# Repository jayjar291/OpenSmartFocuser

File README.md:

# OpenSmartFocuser

OpenSmartFocuser is an open-source telescope focuser project with:
- ESP32-S3 firmware (display/menu, motor control, serial command handling)
- an INDI driver scaffold for host-side integration
- hardware design files for PCB and related fabrication assets

## Build Targets

- `firmware/` contains the PlatformIO project for the device firmware.
- `drivers/indi/` contains the CMake-based INDI focuser driver.

## Folder Structure

```text
OpenSmartFocuser/
├── .github/
│   ├── ISSUE_TEMPLATE/        # GitHub issue templates
│   └── workflows/             # CI workflows (firmware and INDI driver builds)
├── docs/                      # Project documentation and operating notes
├── drivers/
│   └── indi/                  # INDI driver scaffold and CMake config
├── firmware/
│   ├── include/               # Firmware headers/config
│   ├── src/                   # Firmware source code
│   ├── platformio.ini         # PlatformIO project config
│   └── backup/                # Local backup files
└── hardware/
    ├── README.md              # Hardware folder overview
    ├── cad/                   # Mechanical CAD-related files
    │   └── README.md          # CAD file overview
    └── pcb/                   # KiCad project and fabrication outputs
        ├── README.md          # PCB project overview
        └── fabrication/       # Fabrication export guidance and outputs
```

## Continuous Integration

- `firmware-build.yml` builds the firmware project on Ubuntu with PlatformIO.
- `indi-driver-build.yml` configures and builds the INDI driver on Ubuntu with system INDI, Nova, GSL, and ZLIB development packages.

## Local Builds

Firmware:

```bash
cd firmware
pio run
```

INDI driver:

```bash
cd drivers/indi
cmake -S . -B build
cmake --build build --parallel
sudo cmake --install build
sudo udevadm control --reload-rules
sudo udevadm trigger
```

The INDI driver build expects CMake, a C++ compiler, and the development packages for INDI, Nova, GSL, and ZLIB.
The install step also deploys a udev rule that creates the stable serial symlink `/dev/OSF` for OpenSmartFocuser devices (USB VID:PID `1209:F0C1`).

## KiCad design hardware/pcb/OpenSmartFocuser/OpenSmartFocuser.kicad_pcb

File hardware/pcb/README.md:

# PCB

This folder contains the KiCad project and related fabrication assets for the OpenSmartFocuser controller board.

## Folder Structure

```text
pcb/
├── OpenSmartFocuser/  # KiCad project source files
├── fabrication/       # Fabrication export guidance and output files
```

## Contents

- `OpenSmartFocuser/` contains the schematic, board layout, symbols, footprints, and project metadata.
- `fabrication/` is reserved for Gerber, drill, BOM, and pick-and-place outputs.

## Use Case

Use this folder when you need to:

- edit the schematic or PCB layout in KiCad.
- review net names, footprints, and placement.
- generate manufacturer-ready fabrication files.

Keep fabrication exports separate from the source project so the design files remain easy to review and version.

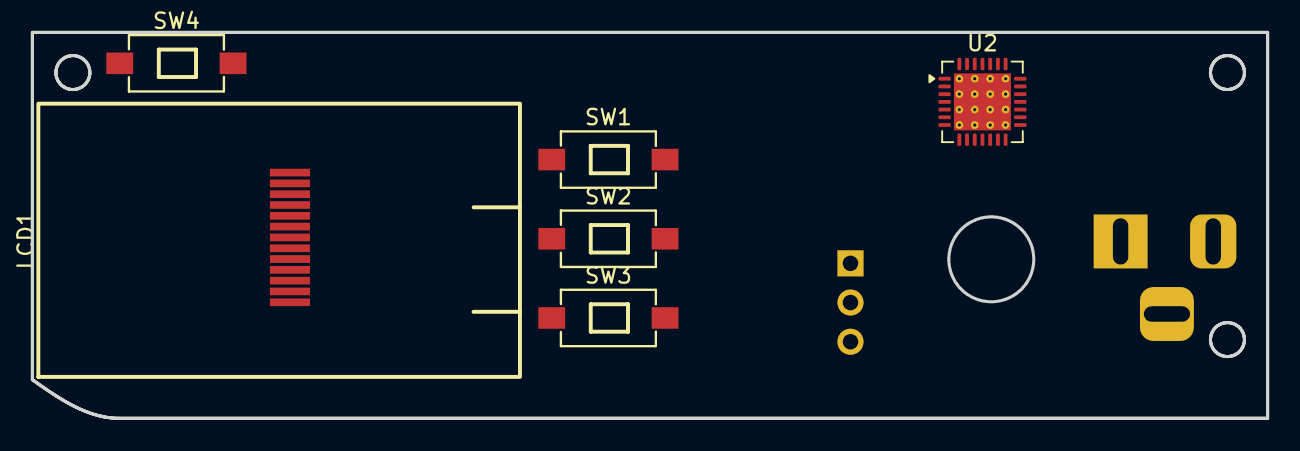
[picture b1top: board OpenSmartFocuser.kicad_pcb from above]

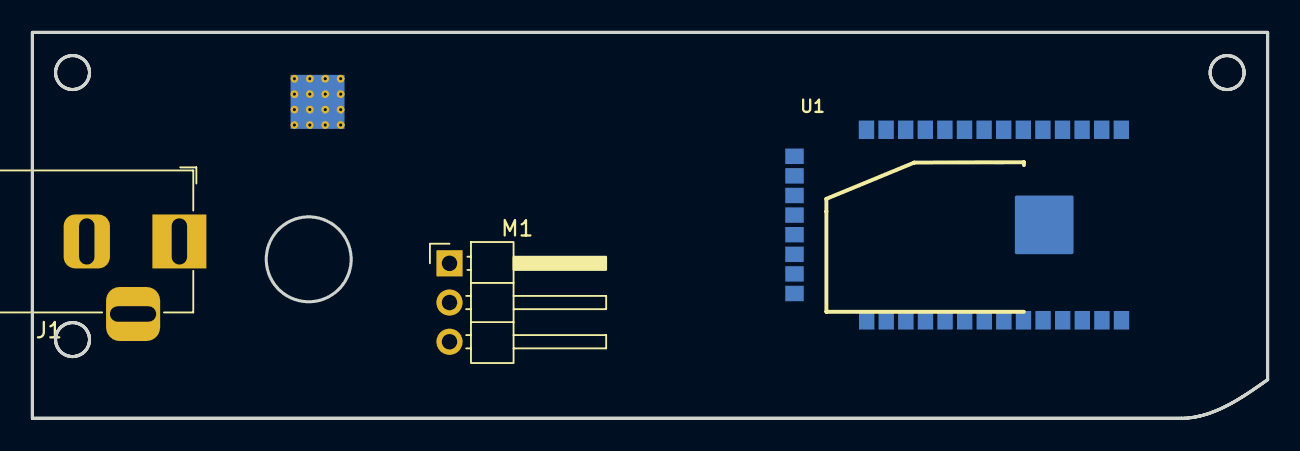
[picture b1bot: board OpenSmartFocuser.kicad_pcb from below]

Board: 2 copper layers, 80.0 x 25.0 mm, 9 parts (3 on the bottom side), 2 nets, no tracks yet.

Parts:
J1: Barrel_Jack_Switch; BarrelJack_Horizontal
LCD1: LCD-SMD_1.14IPS-LCD
M1: Motor_Servo; PinHeader_1x03_P2.54mm_Horizontal
SW1, SW2, SW3, SW4: SW-SMD_L6.0-W3.5-LS8.0-1
U1: NanoS3
U2: TMC2209-LA; VQFN-28-1EP_5x5mm_P0.5mm_EP3.7x3.7mm_ThermalVias

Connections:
unnamed: U2.3 (GND), U2.18 (GND), U2.29 (GND)
unnamed: U2.22 (VS), U2.28 (VS)

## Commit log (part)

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2026-03-07 Initial project structure
2026-03-07 added the kicad files
2026-03-20 removed AI readme files
2026-03-24 Initial functioning hardware and configuration tests
2026-03-25 Refactor pin configuration and driver setup for TMC2209 and ST7789; add TFT_eSPI setup header
2026-03-25 Add custom screens for OpenMenuOS UI; implement idle and preset screens with button handling
2026-03-25 Add LX200 serial command support and star map rendering functionality
    - Implemented LX200 serial command handling in lx200_serial.cpp, allowing for setting and getting the right ascension (RA) and declination (Dec) of the idle star map center.
    - Added functions to format RA and Dec in LX200 string format and parse incoming commands.
    - Introduced star map rendering capabilities in star_map_renderer.cpp, including functions to project stars based on the viewport and field of view (FOV).
    - Added utility functions for color and radius determination based on star magnitude.
2026-03-25 added additional star maps
2026-03-26 Update motion configuration and remove LX200 serial support
    - Increased TMC maximum speed to 80000 and acceleration to 15000.
    - Added homing speed configuration.
    - Removed LX200 serial handling files and references.
2026-03-27 Update motor speed configurations and enhance homing functionality
2026-03-27 Refactor motor control to use FastAccelStepper; update speed and acceleration settings
2026-04-06 Refactor code structure for improved readability and maintainability
2026-04-07 UI overhaul along with Movement overhaul
2026-04-07 Implement serial command handling and debug output features
2026-04-07 Disable serial debug output in configuration
2026-04-07 Fix debug output to use println for framing messages
2026-04-08 Refactor focus speed settings and add speed selection functionality
2026-04-08 Refactor movement and serial command handling
    - Updated the `startHoming` function to streamline the homing process by removing redundant variable assignments and ensuring proper state management.
    - Enhanced the `updateHoming` function to include a response indicating the completion of the homing sequence.
    - Modified the serial command handler to improve command parsing and dispatching, including the addition of new commands for setting targets and handling presets.
    - Introduced a new menu system with structured screens and settings, allowing for better user interaction and configuration.
    - Added string constants for menu titles and options to improve code readability and maintainability.
    -
2026-04-08 Add persistent position handling to movement module
2026-04-09 Implement preset management functionality with commands to add, remove, and list presets
2026-04-09 Comment out unused configuration options in platformio.ini
2026-04-14 Refactor serial command handling by removing unused functions and enhancing argument parsing logic
2026-04-16 Enhance preset management and device info screens with new functionalities and UI updates
2026-05-12 Add motor idle timeout and health check functionality; implement serial commands for current and microsteps
2026-05-12 Add initial INDI driver scaffold with CMake configuration and necessary files
2026-05-12 docs: add concise root README with project summary and folder structure
    Agent-Logs-Url: https://github.com/jayjar291/OpenSmartFocuser/sessions/6ff36525-96a6-4b32-9c91-4aa74a5c1d78
2026-05-12 Add OpenSmartFocuser Dummy Driver Implementation
    - Implemented the OpenSmartFocuserDummy class in indi_opensmartfocuser_focuser.cpp and its corresponding header file.
    - Added methods for connecting, disconnecting, moving the focuser, and managing properties in a simulated environment.
    - Updated XML configuration to reflect the new dummy driver name.
    - Enhanced .gitignore files to exclude build artifacts and IDE-specific files.
    - Introduced CMake modules for finding INDI and NOVA libraries, along with Unity build support.
2026-05-12 implement handleClearTarget command and update command index
2026-05-12 feat: add new serial command handlers for movement, homing, speed, and firmware version
2026-05-13 enhance movement control with endstop handling and speed settings
2026-05-13 remove debug print statement in jogForward function
2026-05-13 add movement status and speed setting retrieval functions
2026-05-13 implement previously unimplemented command handlers for movement and speed retrieval
2026-05-13 add adjustFocusSpeedSetting function and integrate with speed command handler
2026-05-13 add motor control command handlers and integrate with movement functions
2026-05-13 add endstop handling functions and remove duplicate definitions
2026-05-13 refactor OpenSmartFocuser class and update XML configuration for driver
2026-05-15 add serial monitor functionality and speed preset handling
2026-05-15 add detailed comments for driver functionality and property management
2026-05-15 add getLimits function and handleGetLimits command for min/max step retrieval
2026-05-31 add addon support for shutter and flat panel controls with corresponding commands
2026-06-01 add toggle functionality for flat panel and shutter, update pin assignments, and enhance menu options
2026-06-02 update flat frame panel configuration, switch from Adafruit NeoPixel to FastLED, and enhance PWM setup for LCD backlight control
    TODO REMOVE FLAT FRAME
2026-06-03 refactor addon management: remove unused begin function, update flat panel pin configuration, and streamline brightness control
2026-06-03 add limit querying and handling for min/max steps in OpenSmartFocuser
2026-06-03 add support for shutter and flat panel addons: implement properties, commands, and interface updates
2026-06-06 refactor shutter control: update position type to uint16_t, enhance movement logic, and adjust limits
2026-06-06 chore: normalize addon naming and add folder docs
2026-06-06 chore: polish addon naming and comments
2026-06-06 chore: resolve merge conflicts with main
2026-06-08 Initial revision focuser 3D print files and CAD
2026-06-08 Enhance documentation and CI workflows: - Update bug report template to specify component types. - Add build targets and CI details to README. - Create INDI driver build workflow for automated CI. - 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
2026-06-09 update CI workflow to use Ubuntu 24.04, enhance dependency installation, and switch to Debug build type
2026-06-09 Refactor USB handling: update serial interface to Stream, add USB descriptor configurator, and set VID/PID for TinyUSB
2026-06-09 Add udev rules for OpenSmartFocuser USB devices and update shutter angle limits
2026-06-28 Add board configuration for ESP32 S3 mainboard including pin definitions for TMC2209, ST7789 display, LED, buttons, and servos
